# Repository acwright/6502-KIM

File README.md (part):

6502-KIM
========

*(Image shows the alternative Main Board configuration — preferred Backplane/Backplane Pro build pictured separately)*

An **AC6502** retro-style 8-bit computer based on the **65C02** microprocessor.

> 📖 **Guide:** [AC6502 Documentation](https://acwright.github.io/6502-DOCS/) — the user's and programmer's guide for the whole family.
> See [The KIM keypad add-on chapter](https://acwright.github.io/6502-DOCS/addons/kim).

---

**Building one? Every part you need, with supplier numbers and known issues, is in [BOM.md](BOM.md).**

## Table of Contents

- [Overview](#overview)
- [Architecture](#architecture)
- [Systems](#systems)
- [Software](#software)
- [Hardware](#hardware)
  - [KIM Board](#kim-board) *(Rev 1.0 ordered, not yet built)*
  - [Backplane / Backplane Pro](#backplane--backplane-pro) *(preferred)*
  - [CPU Card](#cpu-card) *(preferred)*
  - [Memory Card](#memory-card) *(preferred)*
  - [Serial Card](#serial-card)
  - [Backplane Helper](#backplane-helper)
  - [Keypad Card](#keypad-card)
  - [Keypad Helper](#keypad-helper)
  - [Keypad LCD Helper](#keypad-lcd-helper)
  - [Main Board](#main-board) *(alternative)*
- [Which revision to make](#which-revision-to-make)
- [Firmware](#firmware)
- [CAD](#cad)
- [Production](#production)
- [Schematics](#schematics)
- [Shared lines](#shared-lines)
- [Extra pins: `EXP0`–`EXP3` and `HRDB`](#extra-pins-exp0exp3-and-hrdb)
- [Jumpers](#jumpers)
- [Off-board headers](#off-board-headers)
- [Checking the schematics](#checking-the-schematics)
- [Libraries](#libraries)
- [Bill of Materials](#bill-of-materials)
- [Purchase](#purchase)
- [License](#license)

## Overview

The AC6502 ecosystem is a family of open-source, 65C02-based computers sharing a common architecture, memory map, and [BIOS](https://github.com/acwright/6502-BIOS). Each computer in the family is purpose-built for a different use case but runs the same software and firmware.

The **KIM** (Keypad Input Monitor) is a complete, self-contained 65C02 computer. The preferred way to build it is using a **[Backplane or Backplane Pro](https://github.com/acwright/6502-COB)**, **[CPU Card](https://github.com/acwright/6502-COB)**, and **[Memory Card](https://github.com/acwright/6502-COB)** from the COB project, along with the **[Serial Card](https://github.com/acwright/6502-COB)** and **[Backplane Helper](https://github.com/acwright/6502-COB)** (also from COB) and the **Keypad Card** — a card that the **Keypad Helper** (keypad matrix) and **Keypad LCD Helper** (16x2 LCD display) attach to. As an alternative, the **[Main Board](https://github.com/acwright/6502-VCS)** from the VCS project can be substituted for the Backplane/CPU/Memory combination.

The **[KIM Board](#kim-board)** puts the whole KIM on one through-hole board, with two breadboards for building circuits beside the keypad. Its memory map and I/O addresses are the same as today's KIM, so the KC Monitor, the BIOS and every program run on it unchanged. Rev 1.0 has been ordered. No board has been built or tested yet.

## Architecture

All AC6502 computers share:

- **CPU**: 65C02 (or accurate emulation)
- **Memory**: 32KB RAM + 32KB ROM, with optional banked RAM expansion
- **Memory Map**: Standardized across the ecosystem — zero page, stack, I/O space ($8000–$9FFF), system ROM, and interrupt vectors at $FFFA–$FFFF
- **Bus**: 16-bit address bus, 8-bit bidirectional data bus, standard 65C02 control signals (RW, PHI2, RESET, IRQ, NMI, RDY, SYNC)
- **BIOS**: A common [BIOS](https://github.com/acwright/6502-BIOS) provides the kernel, monitor, and BASIC interpreter across all systems

## Systems

| Project | Description |
|---------|-------------|
| [6502-ACE](https://github.com/acwright/6502-ACE) | All-in-one Computer Experience — A single board computer |
| [6502-COB](https://github.com/acwright/6502-COB) | Computer On a Backplane — Modular desktop computer with expandable card slots |
| [6502-DEV](https://github.com/acwright/6502-DEV) | Development Environment Vehicle — Emulation-based dev system |
| [6502-KIM](https://github.com/acwright/6502-KIM) | Keypad Input Monitor - KIM-1 inspired minimal computer (YOU ARE HERE) |
| [6502-VCS](https://github.com/acwright/6502-VCS) | Video Computer System — Cartridge-based retro gaming console |

## Software

| Project | Description |
|---------|-------------|
| [6502-BIOS](https://github.com/acwright/6502-BIOS) | The shared BIOS (kernel, monitor, BASIC) for all AC6502 computers |
| [6502-EMULATOR](https://github.com/acwright/6502-EMULATOR) | Emulator for the whole family — desktop app, browser build, and a command line for scripted runs |
| [6502-PRG](https://github.com/acwright/6502-PRG) | Template project for writing assembly language programs |
| [6502-CRT](https://github.com/acwright/6502-CRT) | Template project for writing assembly language cartridges |
| [6502-ASM](https://github.com/acwright/6502-ASM) | Assembly language example programs and demos |
| [6502-BAS](https://github.com/acwright/6502-BAS) | BASIC program listings |
| [6502-WOZMON](https://github.com/acwright/6502-WOZMON) | Wozmon as a standalone ROM |
| [6502-NOP](https://github.com/acwright/6502-NOP) | An all-NOP ROM, for probing a board during bring-up |
| [6502-DOCS](https://github.com/acwright/6502-DOCS) | The documentation site — the guide, the printable reference cards, branding and label artwork |
| [cffs](https://github.com/acwright/cffs) | Builds CompactFlash disk images for the BIOS filesystem |
| [bastok](https://github.com/acwright/bastok) | Tokenizes BASIC listings into `.prg` images, and back |
| [bin2woz](https://github.com/acwright/bin2woz) | Converts a binary into a Wozmon serial upload |

## Hardware

This repository contains KiCad 7.0+ PCB designs for the KIM-specific hardware. The KIM Board is the whole KIM on one board. Today's KIM, described after it, also uses boards, cards, and helpers from the [6502-COB](https://github.com/acwright/6502-COB) project, and optionally from the [6502-VCS](https://github.com/acwright/6502-VCS) project.

### KIM Board
`Hardware/KIM Board/`

*Rev 1.0's schematic passes its checks (see [Checking the schematics](#checking-the-schematics)), and its PCB is finished and exported for production (`Production/KIM Board/Rev 1.0/`). The first boards have been ordered. No board has been built or tested yet.*

One through-hole board that joins every part of today's KIM. The computer itself (CPU, RAM, ROM, glue logic and the I/O decode) is the ACE Board Rev 1.1's. The clock, the reset and the power input are the Backplane Pro Rev 1.1's. The serial port is the Serial Card's, and the keypad, the LCD and the KC Monitor are the Keypad Card's, Keypad Helper's and Keypad LCD Helper's. The card slot and the 6502 BUS header are the Backplane Helper's. The keypad, the LCD, the card slot and the 6502 BUS header sit exactly where they are on today's KIM, and the board fits today's base plate. Provides:

- **CPU**: 65C02 (U1) at 1 MHz, clocked by a 1 MHz DIP-14 oscillator (X1)
- **RAM**: 32KB SRAM (AS6C62256, U2)
- **ROM**: 32KB EEPROM (AT28C256, U3) holding the BIOS, on a footprint that takes a ZIF socket or an ordinary one
- **Keypad and display**: W65C21N PIA (U8), the KC Monitor's 8KB AT28C64 (U9) in a plain socket, the 24-key keypad with its MM74C922 encoder (U16), and the 16×2 LCD (U13) with its 10kΩ contrast trimmer (VR1). R19 beside VR1 is not fitted. It is there for a trimmer larger than 10kΩ: a resistor fitted in parallel brings the trimmer near 10kΩ. The PIA's `CB1` and `CB2` are unused; they are joined and held high by R23 (10kΩ), so neither floats. It is a resistor rather than a tie to VCC because software can make `CB2` an output.
- **Serial**: R6551AP ACIA (U15) at `$9000` with a MAX232 (U14) and a 1.8432 MHz crystal (Y1). The female DB-9 (J2) is wired as **DCE**, as on the Serial Card, so a straight-through cable reaches a PC. The `CTS EN` jumper (J3) picks whether the ACIA's `CTS` comes from ground or from the cable. **Ground is the default**, which leaves the transmitter always free to send
- **Reset**: 555 power-on reset (U12, Q1) and a reset button (SW26)
- **Power**: 5V DC, center positive, through a barrel jack (J7), a 1N5819 reverse-polarity diode (D5) and the power switch (SW27)
- **Expansion**: one card slot (J4), the 6502 BUS header (J5), and the breadboards with the breadboard headers (J6)

#### The KIM enable jumper (J1)

J1 is a 3-pin header marked `KIM ENABLE`, with `KIM` printed at pin 1 and `BASIC` at pin 3. One shunt switches the KIM on or off:

- **KIM** (shunt on pins 1 and 2): the machine starts in the KC Monitor, with the keypad and the LCD.
- **BASIC** (shunt on pins 2 and 3): BASIC over the serial port, as today's KIM runs with its Keypad Card pulled. The keypad and the LCD do nothing.
- **Set the jumper to BASIC before fitting a cartridge** in the card slot.

Pin 1 is `KIMB`, pin 2 is GND, and pin 3 isn't connected, so in the BASIC position the shunt only parks on the header. In the KIM position the shunt grounds `KIMB`, which enables the Keypad Card's first 74HC138 (U10, on its `~E1`). In the BASIC position, R15 (10kΩ) holds `KIMB` high, so U10 is disabled and neither the PIA nor the KC Monitor's ROM is ever selected. A BAT85 (D1) joins `KIMB` to `HRDB`, anode on `HRDB`. In the KIM position the shunt pulls `HRDB` low through D1, which takes `$C000–$FFFF` away from the BIOS ROM, as the Keypad Card does today. A cartridge pulling `HRDB` low can't pull `KIMB` low through D1, so only the jumper switches the KIM on.

Reads with `PHI2` high:

| KIM enable | Cartridge | `$0000–$7FFF` | `$8000–$9FFF` | `$A000–$BFFF` | `$C000–$DFFF` | `$E000–$FFFF` |
|---|---|---|---|---|---|---|
| KIM | out | RAM | IO1–IO8 | ROM | PIA | KC Monitor ROM |
| BASIC | out | RAM | IO1–IO8 | ROM | ROM | ROM |
| BASIC | in | RAM | IO1–IO8 | ROM | cartridge | cartridge |
| KIM | in | RAM | IO1–IO8 | ROM | **PIA and cartridge** | **KC Monitor ROM and cartridge** |

The last row is a mistake: the PIA and the KC Monitor's ROM fight the cartridge over the data bus. Set the jumper to BASIC before fitting a cartridge.

With the jumper set to BASIC, `RESB` still resets the PIA. That clears its control registers, so its interrupts stay off and it never pulls `IRQB`. The PIA's own pull-ups hold the LCD's `E` and `R/W` high and turn the keypad encoder's outputs off, so neither the LCD nor the encoder drives anything.

#### The IO ENABLE switch (SW25)

The eight-way DIP switch marked **IO ENABLE** has one position for each of the eight 1KB I/O windows, IO1 to IO8. U7, a 74HC138, decodes `$8000–$9FFF` into the eight windows, and switch *n* passes window *n*'s select through as `IOnB`. With a switch off, a 1kΩ pull-up holds that select high, so nothing in that window is selected.

| Switch | Select | Window | On the board |
|---|---|---|---|
| 1 | `IO1B` | `$8000–$83FF` | breadboard headers only |
| 2 | `IO2B` | `$8400–$87FF` | breadboard headers only |
| 3 | `IO3B` | `$8800–$8BFF` | breadboard headers only |
| 4 | `IO4B` | `$8C00–$8FFF` | breadboard headers only |
| 5 | `IO5B` | `$9000–$93FF` | the serial port's ACIA (U15), and the breadboard headers |
| 6 | `IO6B` | `$9400–$97FF` | breadboard headers only. **IO6** is the window for breadboard circuits |
| 7 | `IO7B` | `$9800–$9BFF` | breadboard headers only |
| 8 | `IO8B` | `$9C00–$9FFF` | breadboard headers only |

Leave switch 5 on: it is the serial port. The others matter only to a breadboard circuit that uses its select. A card in the card slot decodes its own address and doesn't use these switches.

#### The card slot (J4) and the 6502 BUS header (J5)

The card slot takes one COB card or one ACE or VCS cartridge. The 6502 BUS header is a 2×20 box header that takes a ribbon cable to a COB Backplane, which is how the KIM Board grows into a bigger machine. Both carry the same bus as the breadboard headers. `EXP0` and `EXP1` are both `HRDB`, as on the ACE. `EXP2` and `EXP3` are bus lines with nothing on the board attached.

- **A COB card** in the card slot decodes its own address. It must not use IO5, the serial port, or a window a breadboard circuit uses.
- **An ACE or VCS cartridge** in the card slot gets `$C000–$FFFF` while the KIM enable jumper is set to BASIC (the third row of the table above).
- **A COB Backplane** on the 6502 BUS header adds no pull-ups of its own. The KIM Board carries the one 10kΩ pull-up on each shared line (`IRQB`, `NMIB`, `RESB`, `RDY`, `BE`).

#### The breadboards

The bottom-left of the board holds two snap-together breadboards, each 6.5 × 2.25 in, as on today's KIM. The breadboards are where circuits are built: the **breadboard circuits**, the LED latch at `$9400` first. Nothing is mounted under them.

The **breadboard headers** (J6) bring the whole bus and the eight I/O selects to the breadboards. They are one straight strip of female headers just above the breadboards, which jumper wires plug into: a 1×20, a 1×20 and a 1×10, left to right, with one empty pitch between them.

| Header | Pins, left to right |
|---|---|
| Row 1 (the bus's odd pins) | GND, `RESB`, `IRQB`, `NMIB`, `RDY`, `BE`, `RWB`, `SYNC`, `PHI2`, `EXP3`, `EXP2`, `D7`, `D6`, `D5`, `D4`, `D3`, `D2`, `D1`, `D0`, VCC |
| Row 2 (the bus's even pins) | VCC, `EXP1` (`HRDB`), `EXP0` (`HRDB`), `A15`, `A14`, `A13`, `A12`, `A11`, `A10`, `A9`, `A8`, `A7`, `A6`, `A5`, `A4`, `A3`, `A2`, `A1`, `A0`, GND |
| Select | GND, `IO1B`, `IO2B`, `IO3B`, `IO4B`, `IO5B`, `IO6B`, `IO7B`, `IO8B`, VCC |

- **The bus keeps its pin numbers.** Row 1 is the 6502 BUS header's odd pins in order, and Row 2 its even pins, so one pin table describes the 6502 BUS header, the card slot and the breadboard headers.
- **Each header has power at both ends**, so a breadboard circuit finds GND and VCC next to the signals it uses.
- **The selects come after the IO ENABLE switch.** A select reaches the breadboard headers only while its switch is on.

**Rules for breadboard circuits:**

- A circuit drives `D0`–`D7` only while it is selected, `PHI2` is high and `RWB` is high.
- A circuit may pull `IRQB`, `NMIB` and `RESB` low, open-drain, and must never drive them high.
- `IO1B`–`IO8B` are address decodes only, not qualified by `PHI2` or `RWB`, exactly as on the ACE. A circuit qualifies its writes with `PHI2`, as the LED latch does.
- `IO5B` is the board's own serial port. Build in **IO6** (`$9400–$97FF`), the window the series uses for its breadboard circuits.
- At boot, the Kernal probes for the cards it knows, and the probe reads and writes their windows. A circuit in a window other than IO6 should expect to be read and written at boot.
- A circuit that pulls `HRDB` (`EXP0`/`EXP1`) low takes `$C000–$FFFF` from the ROM, as a cartridge does. D1 keeps it from switching the KIM on.

The LED latch's schematic is the one-page KIM Demo sheet in [6502-DOCS](https://github.com/acwright/6502-DOCS). It decodes `$9400` with its own 74HC138 from `A10`–`A15`, so it doesn't need `IO6B`. `IO6B` on the breadboard headers offers the same select ready-made, for later circuits.

### Backplane / Backplane Pro
[`Hardware/Backplane/`](https://github.com/acwright/6502-COB/tree/main/Hardware/Backplane) *(6502-COB — preferred)*

Passive backplane providing 5 card slots with full bus interconnect across all slots. The **Backplane Pro** is an enhanced variant with integrated clock generation, reset circuitry, and power distribution.

### CPU Card
[`Hardware/CPU Card/`](https://github.com/acwright/6502-COB/tree/main/Hardware/CPU%20Card) *(6502-COB — preferred)*

Hosts the 65C02 CPU in a card form factor. Plugs into the Backplane or Backplane Pro.

### Memory Card
[`Hardware/Memory Card/`](https://github.com/acwright/6502-COB/tree/main/Hardware/Memory%20Card) *(6502-COB — preferred)*

Provides 32KB SRAM and 32KB EEPROM with address decoding logic. Plugs into the Backplane or Backplane Pro.

### Serial Card
[`Hardware/Serial Card/`](https://github.com/acwright/6502-COB/tree/main/Hardware/Serial%20Card) *(6502-COB)*

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
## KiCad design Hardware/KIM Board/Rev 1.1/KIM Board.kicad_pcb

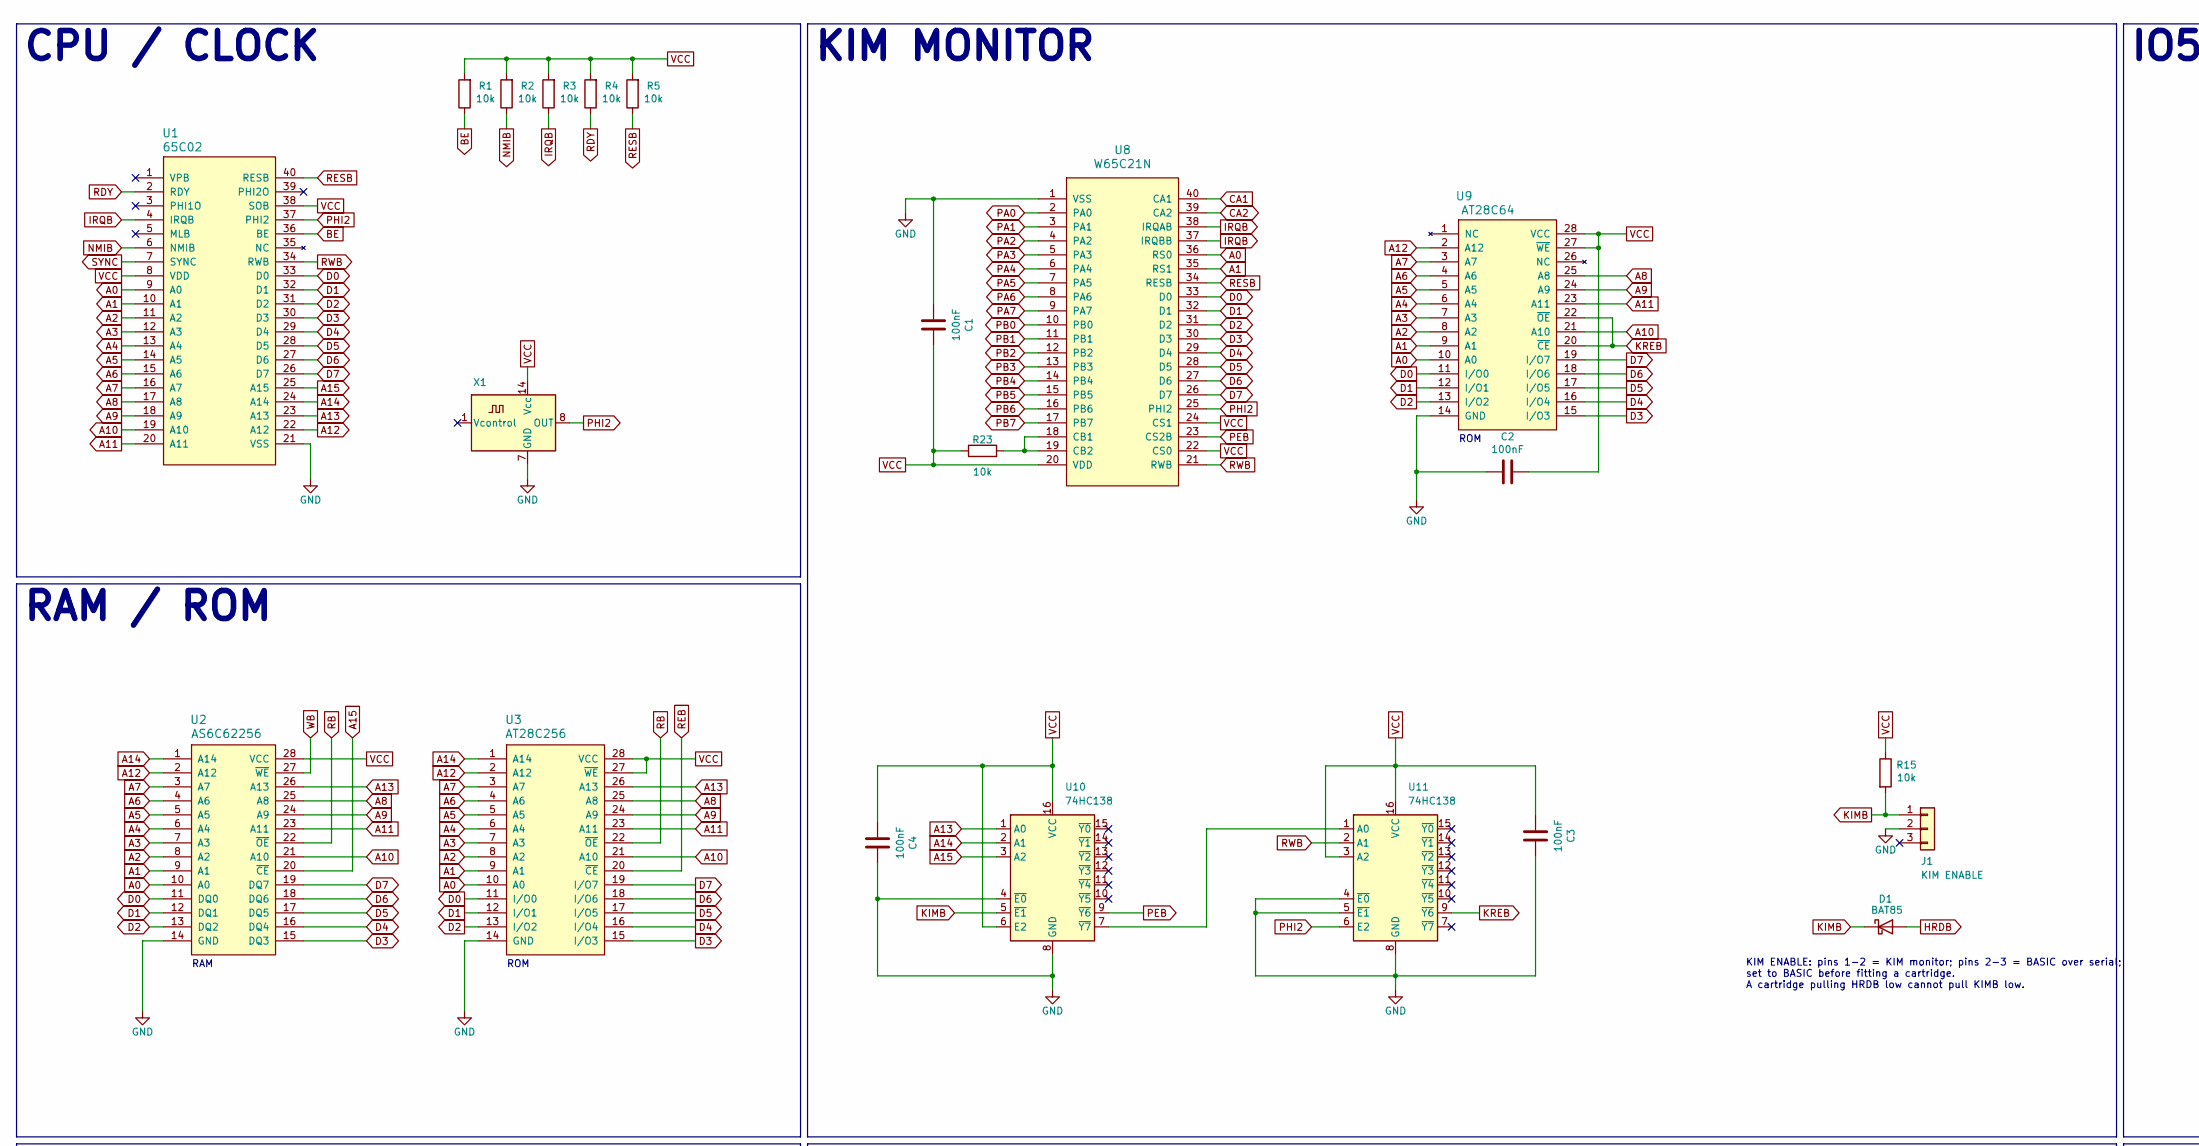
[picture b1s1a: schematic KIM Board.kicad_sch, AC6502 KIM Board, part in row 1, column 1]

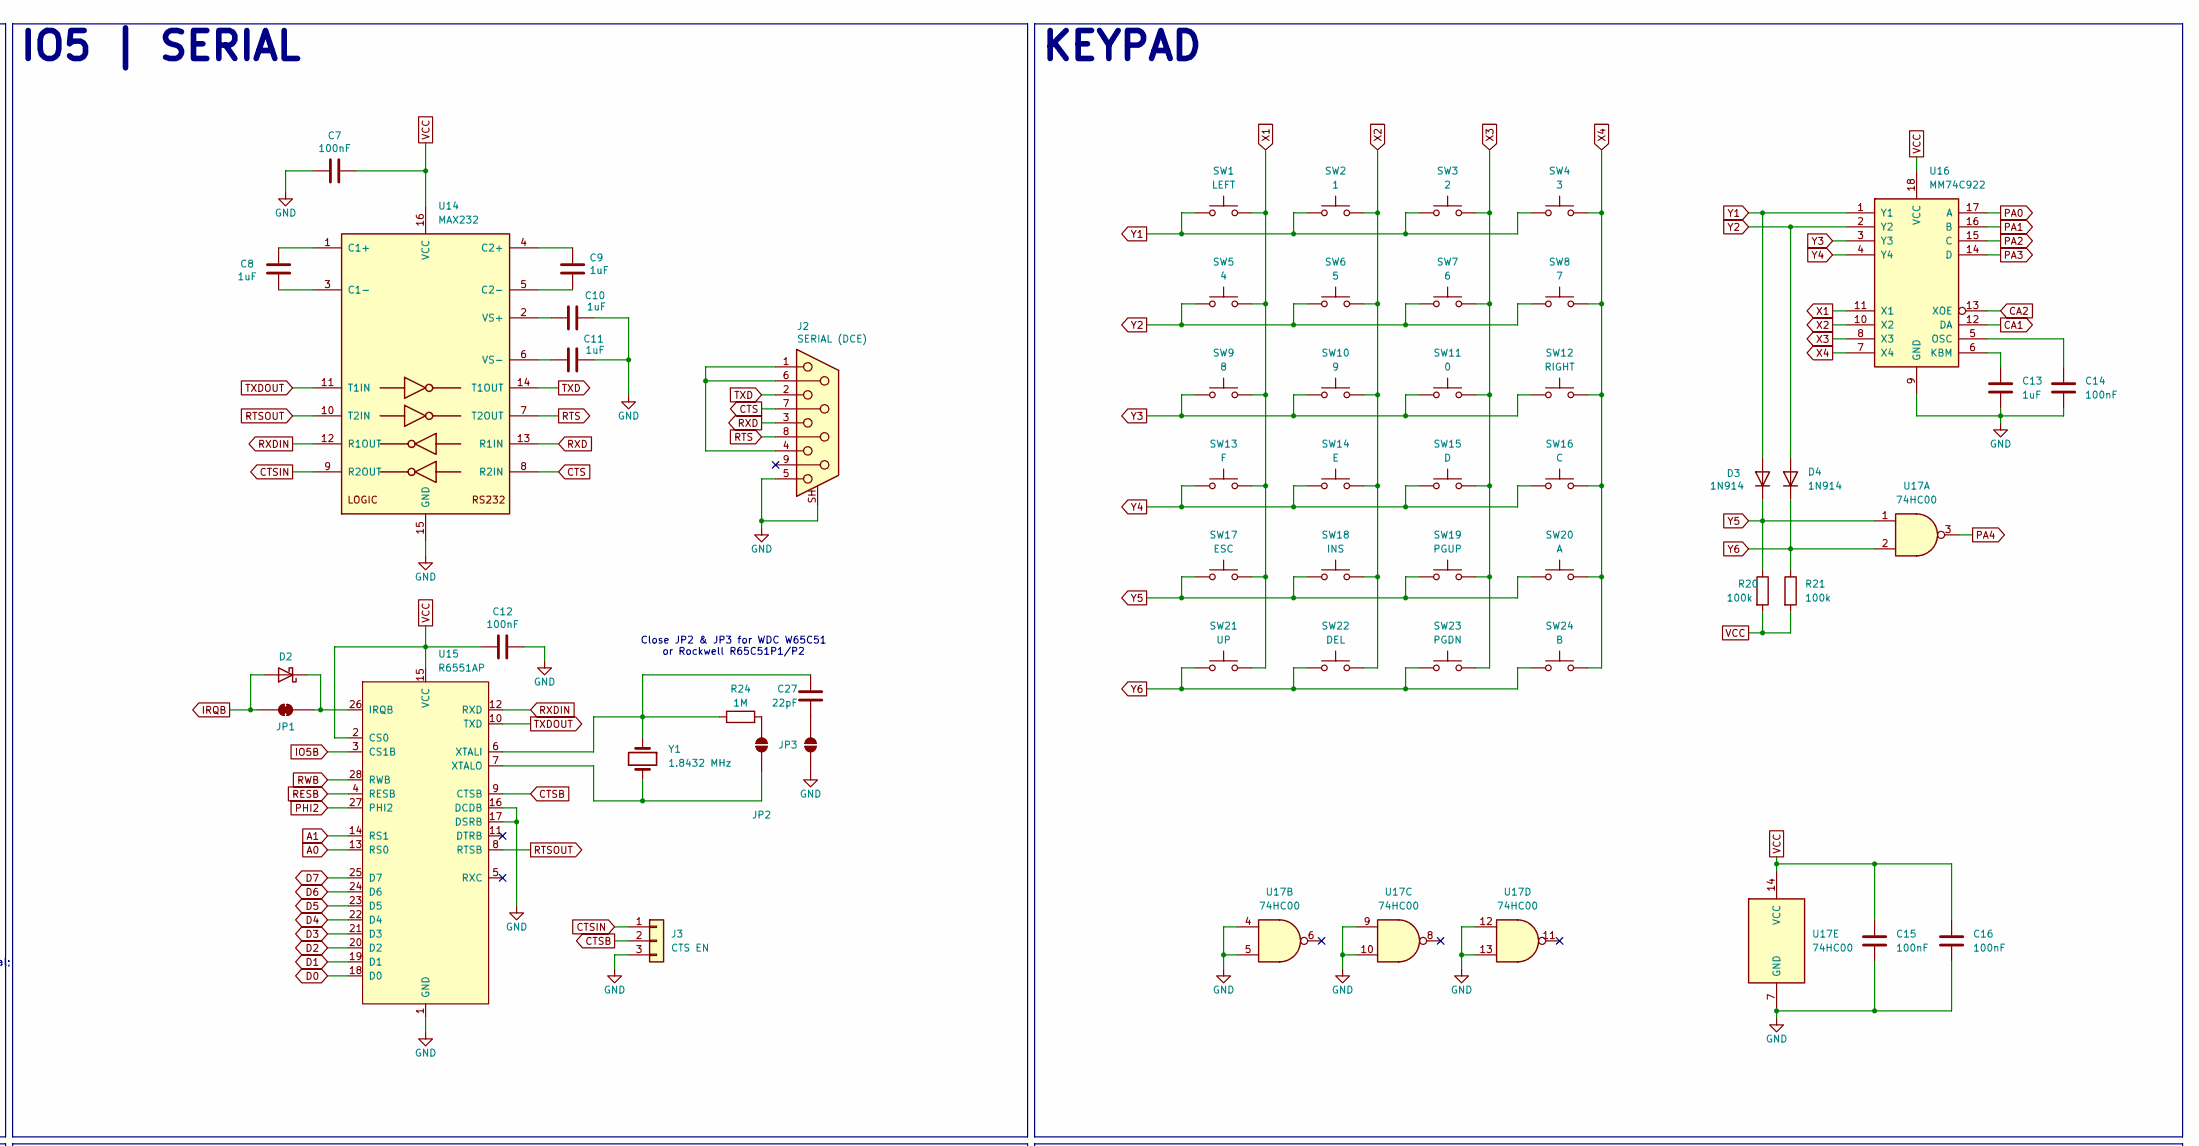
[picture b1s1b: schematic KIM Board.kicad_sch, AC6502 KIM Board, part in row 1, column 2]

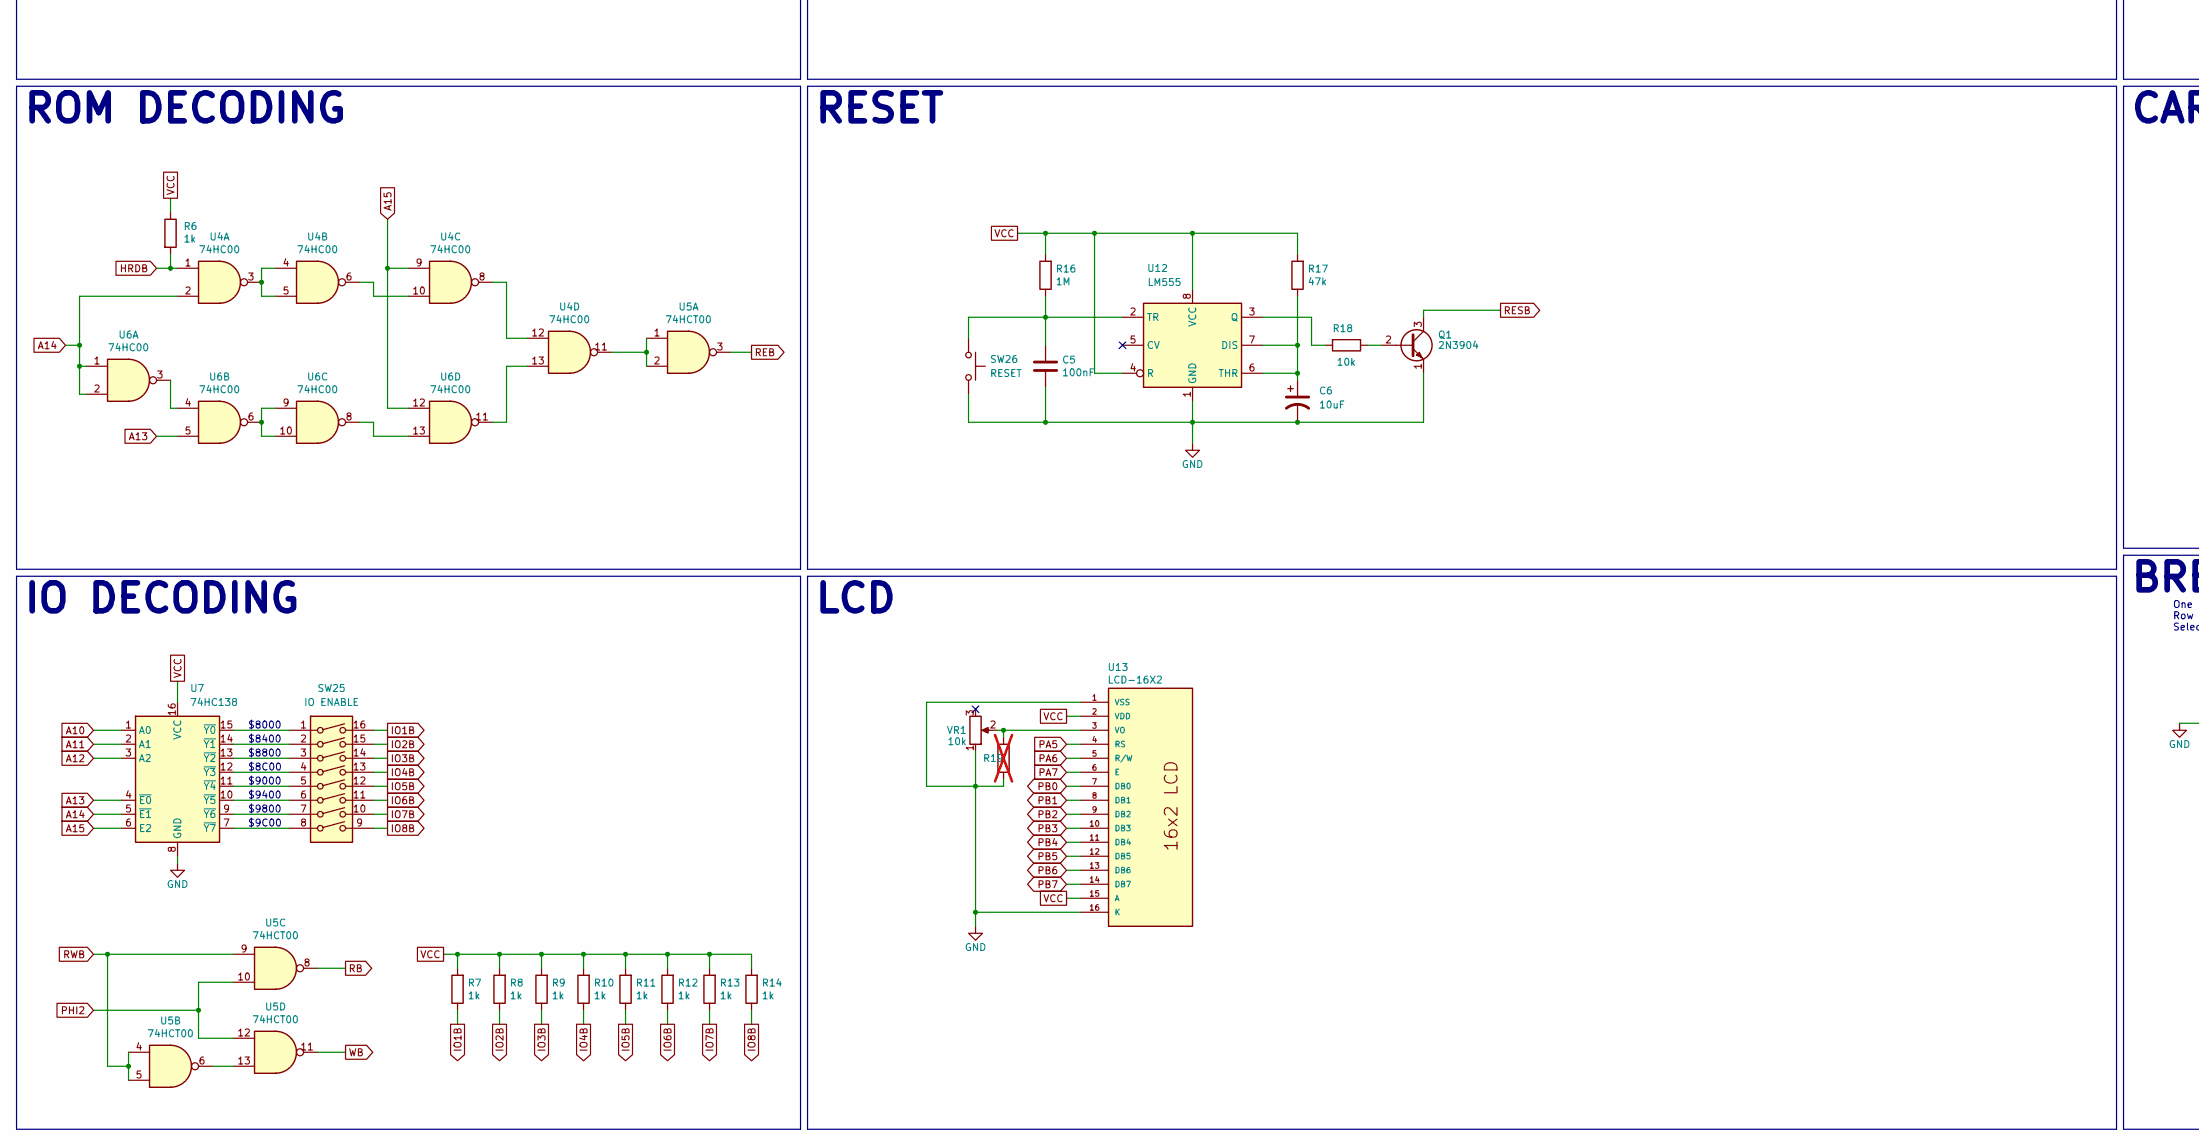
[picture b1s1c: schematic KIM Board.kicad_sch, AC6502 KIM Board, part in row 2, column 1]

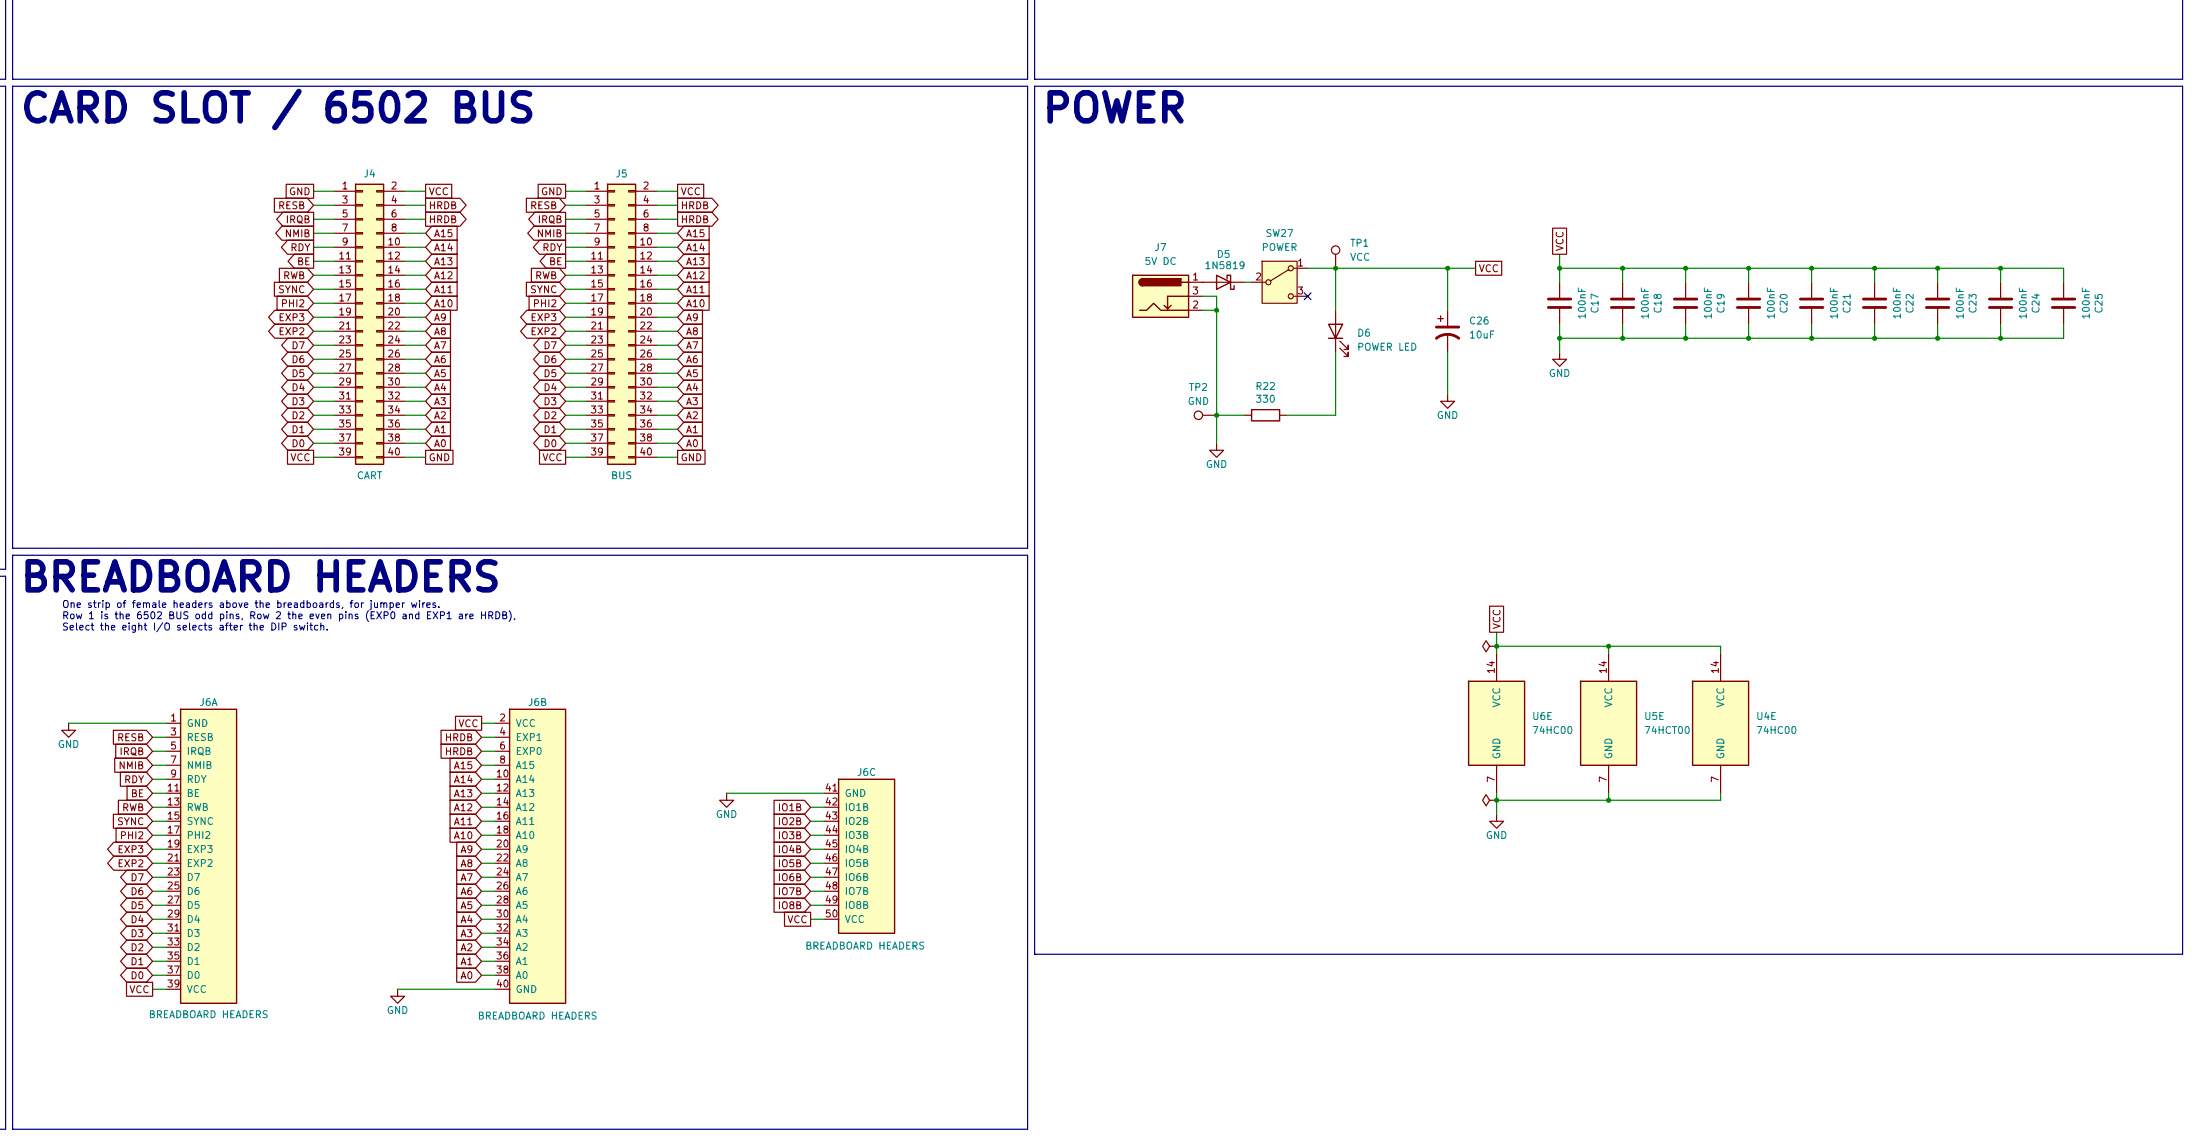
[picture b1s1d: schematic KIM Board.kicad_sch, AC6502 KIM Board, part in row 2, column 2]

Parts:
C1, C2, C3, C4, C5, C7, C12, C14, C15, C16, C17, C18, C19, C20, C21, C22, C23, C24, C25: 100nF; C_Disc_D5.0mm_W2.5mm_P2.50mm; Digikey 478-3187-ND
C6, C26: 10uF; CP_Radial_D4.0mm_P1.50mm; Digikey P14482-ND
C8, C9, C10, C11, C13: 1uF; C_Disc_D5.0mm_W2.5mm_P2.50mm; Digikey 478-7667-ND
C27: 22pF; C_Disc_D5.0mm_W2.5mm_P2.50mm; Digikey 478-4846-ND
D1, D2: BAT85; D_DO-35_SOD27_P7.62mm_Horizontal; Digikey BAT85SCT-ND
D3, D4: 1N914; D_DO-35_SOD27_P7.62mm_Horizontal; Digikey 1N914FS-ND
D5: 1N5819; D_DO-41_SOD81_P10.16mm_Horizontal; Digikey 1N5819-E3/54GICT-ND
D6: POWER LED; LED_D3.0mm; Digikey 732-5008-ND
J1: KIM ENABLE; PinHeader_1x03_P2.54mm_Vertical; Digikey S1011EC-40-ND
J2: SERIAL (DCE); DSUB-9_Socket_Horizontal_P2.77x2.84mm_EdgePinOffset7.70mm_H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; Digikey 609-1487-ND
J3: CTS EN; PinHeader_1x03_P2.54mm_Vertical; Digikey S1011EC-40-ND
J4: CART; 6502 Card Slot; Digikey A31723-ND
J5: BUS; 6502 Bus Connector; Digikey 732-5401-ND
J6: BREADBOARD HEADERS; KIM Breadboard Headers
J7: 5V DC; BarrelJack_Horizontal; Digikey CP-102AH-ND
JP1: SolderJumper_2_Bridged; SolderJumper-2_P1.3mm_Bridged_RoundedPad1.0x1.5mm
JP2, JP3: SolderJumper_2_Open; SolderJumper-2_P1.3mm_Open_RoundedPad1.0x1.5mm
Q1: 2N3904; TO-92_Inline; Digikey 2N3904FS-ND
R1, R2, R3, R4, R5, R15, R18, R23: 10k; R_Axial_DIN0204_L3.6mm_D1.6mm_P5.08mm_Horizontal; Digikey 13-MFR-12FTF52-10KCT-ND
R6, R7, R8, R9, R10, R11, R12, R13, R14: 1k; R_Axial_DIN0204_L3.6mm_D1.6mm_P5.08mm_Horizontal; Digikey 13-MFR-12FTF52-1KCT-ND
R16, R24: 1M; R_Axial_DIN0204_L3.6mm_D1.6mm_P5.08mm_Horizontal; Digikey 13-MFR-12FTF52-1MCT-ND
R17: 47k; R_Axial_DIN0204_L3.6mm_D1.6mm_P5.08mm_Horizontal; Digikey 13-MFR-12FTF52-47KCT-ND
R19: DNP: parallel with VR1 to make ~10 k; R_Axial_DIN0204_L3.6mm_D1.6mm_P5.08mm_Horizontal; not fitted
R20, R21: 100k; R_Axial_DIN0204_L3.6mm_D1.6mm_P5.08mm_Horizontal; Digikey 13-MFR-12FTF52-100KCT-ND
R22: 330; R_Axial_DIN0204_L3.6mm_D1.6mm_P5.08mm_Horizontal; Digikey 13-MFR-12FTF52-330RCT-ND
SW1: LEFT; SW_Cherry_MX_1.00u_PCB; Digikey 1644-MX2A-E1NA-ND
SW2: 1; SW_Cherry_MX_1.00u_PCB; Digikey 1644-MX2A-E1NA-ND
SW3: 2; SW_Cherry_MX_1.00u_PCB; Digikey 1644-MX2A-E1NA-ND
SW4: 3; SW_Cherry_MX_1.00u_PCB; Digikey 1644-MX2A-E1NA-ND
SW5: 4; SW_Cherry_MX_1.00u_PCB; Digikey 1644-MX2A-E1NA-ND
SW6: 5; SW_Cherry_MX_1.00u_PCB; Digikey 1644-MX2A-E1NA-ND
SW7: 6; SW_Cherry_MX_1.00u_PCB; Digikey 1644-MX2A-E1NA-ND
SW8: 7; SW_Cherry_MX_1.00u_PCB; Digikey 1644-MX2A-E1NA-ND
SW9: 8; SW_Cherry_MX_1.00u_PCB; Digikey 1644-MX2A-E1NA-ND
SW10: 9; SW_Cherry_MX_1.00u_PCB; Digikey 1644-MX2A-E1NA-ND
SW11: 0; SW_Cherry_MX_1.00u_PCB; Digikey 1644-MX2A-E1NA-ND
SW12: RIGHT; SW_Cherry_MX_1.00u_PCB; Digikey 1644-MX2A-E1NA-ND
SW13: F; SW_Cherry_MX_1.00u_PCB; Digikey 1644-MX2A-E1NA-ND
SW14: E; SW_Cherry_MX_1.00u_PCB; Digikey 1644-MX2A-E1NA-ND
SW15: D; SW_Cherry_MX_1.00u_PCB; Digikey 1644-MX2A-E1NA-ND
SW16: C; SW_Cherry_MX_1.00u_PCB; Digikey 1644-MX2A-E1NA-ND
SW17: ESC; SW_Cherry_MX_1.00u_PCB; Digikey 1644-MX2A-E1NA-ND
SW18: INS; SW_Cherry_MX_1.00u_PCB; Digikey 1644-MX2A-E1NA-ND
SW19: PGUP; SW_Cherry_MX_1.00u_PCB; Digikey 1644-MX2A-E1NA-ND
SW20: A; SW_Cherry_MX_1.00u_PCB; Digikey 1644-MX2A-E1NA-ND
SW21: UP; SW_Cherry_MX_1.00u_PCB; Digikey 1644-MX2A-E1NA-ND
SW22: DEL; SW_Cherry_MX_1.00u_PCB; Digikey 1644-MX2A-E1NA-ND
SW23: PGDN; SW_Cherry_MX_1.00u_PCB; Digikey 1644-MX2A-E1NA-ND
SW24: B; SW_Cherry_MX_1.00u_PCB; Digikey 1644-MX2A-E1NA-ND
SW25: IO ENABLE; SW_DIP_SPSTx08_Slide_9.78x22.5mm_W7.62mm_P2.54mm; Digikey CT2068-ND
SW26: RESET; SW_PUSH_6mm; Digikey 2223-TS02-66-50-BK-160-LCR-D-ND
SW27: POWER; Power Switch; Digikey EG4326-ND
TP1: VCC; TestPoint_Pad_2.5x2.5mm
TP2: GND; TestPoint_Pad_2.5x2.5mm
U1: 65C02; DIP-40_W15.24mm_Socket_LongPads; Mouser 955-W65C02S6TPG-14
U2: AS6C62256; DIP-28_W15.24mm_Socket_LongPads; Digikey 1450-1033-ND
U3: AT28C256; DIP_Socket-28_W11.9mm_W12.7mm_W15.24mm_W17.78mm_W18.5mm_3M_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; Digikey AT28C256-15PU-ND
U4, U6, U17: 74HC00; DIP-14_W7.62mm_Socket_LongPads; Digikey 296-1563-5-ND
U5: 74HCT00; DIP-14_W7.62mm_Socket_LongPads; Digikey 296-1603-5-ND
U7, U10, U11: 74HC138; DIP-16_W7.62mm_Socket_LongPads; Digikey 296-1575-5-ND
U8: W65C21N; DIP-40_W15.24mm_Socket_LongPads; Mouser 955-W65C21N6TPG-14
U9: AT28C64; DIP-28_W15.24mm_Socket_LongPads; Digikey AT28C64B-15PU-ND
U12: LM555; DIP-8_W7.62mm_Socket_LongPads; Digikey LM555CNNS/NOPB-ND
U13: LCD-16X2
U14: MAX232; DIP-16_W7.62mm_Socket_LongPads; Digikey 296-1402-5-ND
U15: R6551AP; DIP-28_W15.24mm_Socket_LongPads
U16: MM74C922; DIP-18_W7.62mm_Socket_LongPads
VR1: 10k; Trimmer 3386F; Digikey 3386F-103LF-ND
X1: 1 MHz; Oscillator_DIP-14; Digikey X937-ND
Y1: 1.8432 MHz; Crystal_HC49-U_Vertical; Digikey 535-9009-ND

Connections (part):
A0: J4.38, J5.38, J6.38 (A0), U1.9 (A0), U2.10 (A0), U3.10 (A0), U8.36 (RS0), U9.10 (A0), U15.13 (RS0)
A1: J4.36, J5.36, J6.36 (A1), U1.10 (A1), U2.9 (A1), U3.9 (A1), U8.35 (RS1), U9.9 (A1), U15.14 (RS1)
A2: J4.34, J5.34, J6.34 (A2), U1.11 (A2), U2.8 (A2), U3.8 (A2), U9.8 (A2)
A3: J4.32, J5.32, J6.32 (A3), U1.12 (A3), U2.7 (A3), U3.7 (A3), U9.7 (A3)
A4: J4.30, J5.30, J6.30 (A4), U1.13 (A4), U2.6 (A4), U3.6 (A4), U9.6 (A4)
A5: J4.28, J5.28, J6.28 (A5), U1.14 (A5), U2.5 (A5), U3.5 (A5), U9.5 (A5)
A6: J4.26, J5.26, J6.26 (A6), U1.15 (A6), U2.4 (A6), U3.4 (A6), U9.4 (A6)
A7: J4.24, J5.24, J6.24 (A7), U1.16 (A7), U2.3 (A7), U3.3 (A7), U9.3 (A7)
A8: J4.22, J5.22, J6.22 (A8), U1.17 (A8), U2.25 (A8), U3.25 (A8), U9.25 (A8)
A9: J4.20, J5.20, J6.20 (A9), U1.18 (A9), U2.24 (A9), U3.24 (A9), U9.24 (A9)
A10: J4.18, J5.18, J6.18 (A10), U1.19 (A10), U2.21 (A10), U3.21 (A10), U7.1 (A0), U9.21 (A10)
A11: J4.16, J5.16, J6.16 (A11), U1.20 (A11), U2.23 (A11), U3.23 (A11), U7.2 (A1), U9.23 (A11)
A12: J4.14, J5.14, J6.14 (A12), U1.22 (A12), U2.2 (A12), U3.2 (A12), U7.3 (A2), U9.2 (A12)
A13: J4.12, J5.12, J6.12 (A13), U1.23 (A13), U2.26 (A13), U3.26 (A13), U6.5, U7.4 (~E0), U10.1 (A0)
A14: J4.10, J5.10, J6.10 (A14), U1.24 (A14), U2.1 (A14), U3.1 (A14), U4.2, U6.1, U6.2, U7.5 (~E1), U10.2 (A1)
A15: J4.8, J5.8, J6.8 (A15), U1.25 (A15), U2.20 (~CE), U4.9, U6.12, U7.6 (E2), U10.3 (A2)
BE: J4.11, J5.11, J6.11 (BE), R1.1, U1.36 (BE)
CA1: U8.40 (CA1), U16.12 (DA)
CA2: U8.39 (CA2), U16.13 (XOE)
CTS: J2.7, U14.8 (R2IN)
CTSB: J3.2, U15.9 (CTSB)
CTSIN: J3.1, U14.9 (R2OUT)
D0: J4.37, J5.37, J6.37 (D0), U1.33 (D0), U2.11 (DQ0), U3.11 (I/O0), U8.33 (D0), U9.11 (I/O0), U15.18 (D0)
D1: J4.35, J5.35, J6.35 (D1), U1.32 (D1), U2.12 (DQ1), U3.12 (I/O1), U8.32 (D1), U9.12 (I/O1), U15.19 (D1)
D2: J4.33, J5.33, J6.33 (D2), U1.31 (D2), U2.13 (DQ2), U3.13 (I/O2), U8.31 (D2), U9.13 (I/O2), U15.20 (D2)
D3: J4.31, J5.31, J6.31 (D3), U1.30 (D3), U2.15 (DQ3), U3.15 (I/O3), U8.30 (D3), U9.15 (I/O3), U15.21 (D3)
D4: J4.29, J5.29, J6.29 (D4), U1.29 (D4), U2.16 (DQ4), U3.16 (I/O4), U8.29 (D4), U9.16 (I/O4), U15.22 (D4)
D5: J4.27, J5.27, J6.27 (D5), U1.28 (D5), U2.17 (DQ5), U3.17 (I/O5), U8.28 (D5), U9.17 (I/O5), U15.23 (D5)
D6: J4.25, J5.25, J6.25 (D6), U1.27 (D6), U2.18 (DQ6), U3.18 (I/O6), U8.27 (D6), U9.18 (I/O6), U15.24 (D6)
D7: J4.23, J5.23, J6.23 (D7), U1.26 (D7), U2.19 (DQ7), U3.19 (I/O7), U8.26 (D7), U9.19 (I/O7), U15.25 (D7)
EXP2: J4.21, J5.21, J6.21 (EXP2)
EXP3: J4.19, J5.19, J6.19 (EXP3)
GND: C1.1, C2.2, C3.2, C4.2, C5.2, C6.2, C7.1, C10.2, C11.2, C12.2, C13.2, C14.2, C15.2, C16.2, C17.2, C18.2, C19.2, C20.2, C21.2, C22.2, C23.2, C24.2, C25.2, C26.2, J1.2, J2.5, J2.SH (PAD), J3.3, J4.1, J4.40, J5.1, J5.40, J6.1 (GND), J6.40 (GND), J6.41 (GND), J7.2, J7.3, JP3.1 (A), Q1.1 (E), R19.2, R22.2, SW26.2, TP2.1 (1_1), U1.21 (VSS), U2.14 (GND), U3.14 (GND), U4.7 (GND), U5.7 (GND), U6.7 (GND), U7.8 (GND), U8.1 (VSS), U9.14 (GND), U10.4 (~E0), U10.8 (GND), U11.4 (~E0), U11.5 (~E1), U11.8 (GND), U12.1 (GND), U13.1 (VSS), U13.16 (K), U14.15 (GND), U15.1 (GND), U15.16 (DCDB), U15.17 (DSRB), U16.9 (GND), U17.4, U17.5, U17.7 (GND), U17.9, U17.10, U17.12, U17.13, VR1.1, X1.7 (GND)
HRDB: D1.2 (A), J4.4, J4.6, J5.4, J5.6, J6.4 (EXP1), J6.6 (EXP0), R6.2, U4.1
IO1B: J6.42 (IO1B), R7.1, SW25.16
IO2B: J6.43 (IO2B), R8.1, SW25.15
IO3B: J6.44 (IO3B), R9.1, SW25.14
IO4B: J6.45 (IO4B), R10.1, SW25.13
IO5B: J6.46 (IO5B), R11.1, SW25.12, U15.3 (CS1B)
IO6B: J6.47 (IO6B), R12.1, SW25.11
IO7B: J6.48 (IO7B), R13.1, SW25.10
IO8B: J6.49 (IO8B), R14.1, SW25.9
IRQB: D2.2 (A), J4.5, J5.5, J6.5 (IRQB), JP1.1 (A), R3.1, U1.4 (IRQB), U8.37 (IRQBB), U8.38 (IRQAB)
KIMB: D1.1 (K), J1.1, R15.2, U10.5 (~E1)
KREB: U9.20 (~CE), U9.22 (~OE), U11.9 (~Y6)
NMIB: J4.7, J5.7, J6.7 (NMIB), R2.1, U1.6 (NMIB)
unnamed: D2.1 (K), JP1.2 (B), U15.26 (IRQB)
unnamed: D5.2 (A), J7.1
unnamed: D5.1 (K), SW27.2 (B)
unnamed: D6.1 (K), R22.1
unnamed: J2.1, J2.4, J2.6
unnamed: JP2.1 (A), U15.7 (XTALO), Y1.2
unnamed: JP2.2 (B), R24.2
unnamed: C27.2, JP3.2 (B)
unnamed: Q1.2 (B), R18.1
unnamed: U4.3, U4.4, U4.5
unnamed: U4.6, U4.10
unnamed: U4.11, U5.1, U5.2
unnamed: U4.8, U4.12
unnamed: U4.13, U6.11
unnamed: U5.6, U5.13
unnamed: U6.3, U6.4
unnamed: U6.6, U6.9, U6.10
unnamed: U6.8, U6.13
unnamed: SW25.1, U7.15 (~Y0)
unnamed: SW25.2, U7.14 (~Y1)
unnamed: SW25.3, U7.13 (~Y2)
unnamed: SW25.4, U7.12 (~Y3)
unnamed: SW25.5, U7.11 (~Y4)
unnamed: SW25.6, U7.10 (~Y5)
unnamed: SW25.7, U7.9 (~Y6)
unnamed: SW25.8, U7.7 (~Y7)
unnamed: R23.2, U8.18 (CB1), U8.19 (CB2)
unnamed: U10.7 (~Y7), U11.1 (A0)
unnamed: C6.1, R17.1, U12.6 (THR), U12.7 (DIS)
unnamed: R18.2, U12.3 (Q)
unnamed: C5.1, R16.1, SW26.1, U12.2 (TR)
unnamed: R19.1, U13.3 (VO), VR1.2
unnamed: C8.1, U14.1 (C1+)
unnamed: C8.2, U14.3 (C1-)
unnamed: C9.1, U14.4 (C2+)
unnamed: C9.2, U14.5 (C2-)
unnamed: C10.1, U14.2 (VS+)
unnamed: C11.1, U14.6 (VS-)
unnamed: C27.1, R24.1, U15.6 (XTALI), Y1.1
unnamed: C13.1, U16.6 (KBM)
unnamed: C14.1, U16.5 (OSC)
PA0: U8.2 (PA0), U16.17 (A)
PA1: U8.3 (PA1), U16.16 (B)
PA2: U8.4 (PA2), U16.15 (C)
PA3: U8.5 (PA3), U16.14 (D)
PA4: U8.6 (PA4), U17.3
PA5: U8.7 (PA5), U13.4 (RS)
PA6: U8.8 (PA6), U13.5 (R/W)
PA7: U8.9 (PA7), U13.6 (E)
PB0: U8.10 (PB0), U13.7 (DB0)
PB1: U8.11 (PB1), U13.8 (DB1)
PB2: U8.12 (PB2), U13.9 (DB2)
PB3: U8.13 (PB3), U13.10 (DB3)
PB4: U8.14 (PB4), U13.11 (DB4)
PB5: U8.15 (PB5), U13.12 (DB5)
PB6: U8.16 (PB6), U13.13 (DB6)
PB7: U8.17 (PB7), U13.14 (DB7)
PEB: U8.23 (CS2B), U10.9 (~Y6)
PHI2: J4.17, J5.17, J6.17 (PHI2), U1.37 (PHI2), U5.10, U5.12, U8.25 (PHI2), U11.6 (E2), U15.27 (PHI2), X1.8 (OUT)
RB: U2.22 (~OE), U3.22 (~OE), U5.8
RDY: J4.9, J5.9, J6.9 (RDY), R4.1, U1.2 (RDY)
REB: U3.20 (~CE), U5.3
RESB: J4.3, J5.3, J6.3 (RESB), Q1.3 (C), R5.1, U1.40 (RESB), U8.34 (RESB), U15.4 (RESB)
RTS: J2.8, U14.7 (T2OUT)
RTSOUT: U14.10 (T2IN), U15.8 (RTSB)
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
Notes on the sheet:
$9400
$9C00
ROM
$8400
Close JP2 & JP3 for WDC W65C51 or Rockwell R65C51P1/P2
$8800
$8C00
RAM
One strip of female headers above the breadboards, for jumper wires. Row 1 is the 6502 BUS odd pins, Row 2 the even pins (EXP0 and EXP1 are HRDB), Select the eight I/O selects after the DIP switch.
$9000
$9800
$8000
KIM ENABLE: pins 1-2 = KIM monitor; pins 2-3 = BASIC over serial; set to BASIC before fitting a cartridge. A cartridge pulling HRDB low cannot pull KIMB low.
BREADBOARD HEADERS
LCD
IO DECODING
CPU / CLOCK
RESET
KEYPAD
RAM / ROM
POWER
KIM MONITOR
ROM DECODING
IO5 | SERIAL
CARD SLOT / 6502 BUS

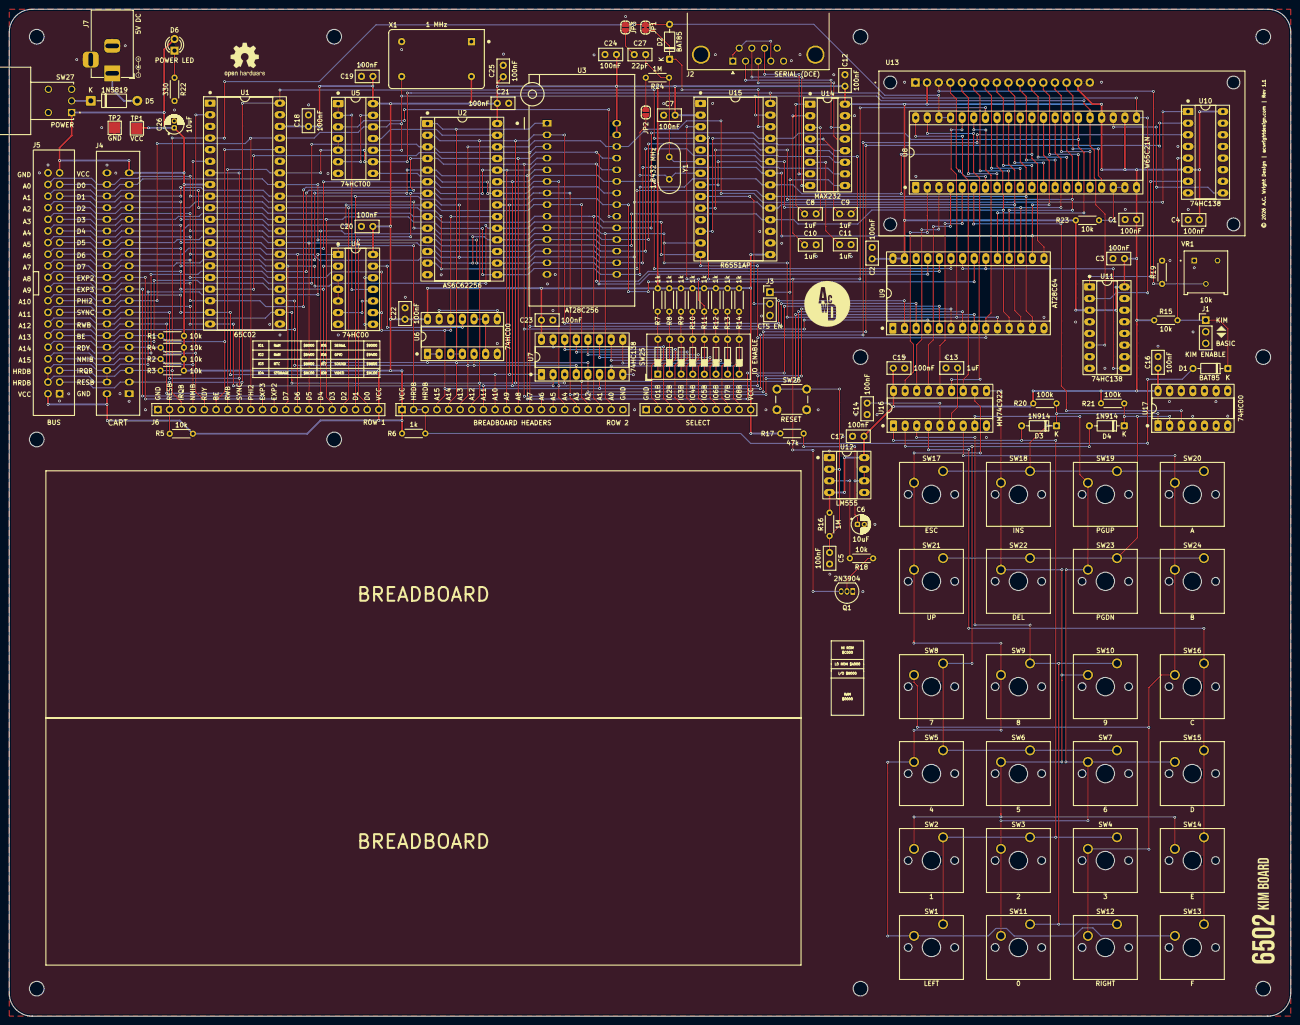
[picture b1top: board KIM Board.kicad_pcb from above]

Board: 2 copper layers, 280.0 x 220.0 mm, 128 parts (0 on the bottom side), 129 nets.

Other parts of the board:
H1, H2, H3, H4, H5, H7, H8, H9, H10, H12, H16: MountingHole; MountingHole_3.2mm_M3

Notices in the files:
README.md:
License:
Hardware designs are released under the [CERN Open Hardware Licence Version 2 – Permissive](https://ohwr.org/cern_ohl_p_v2.txt).
Firmware is released under the [MIT License](./Firmware/KC%20Monitor/LICENSE).
Hardware/KIM Board/Rev 1.1/KIM Board.kicad_pcb:
© 2026 A.C. Wright Design | acwrightdesign.com | Rev 1.1
